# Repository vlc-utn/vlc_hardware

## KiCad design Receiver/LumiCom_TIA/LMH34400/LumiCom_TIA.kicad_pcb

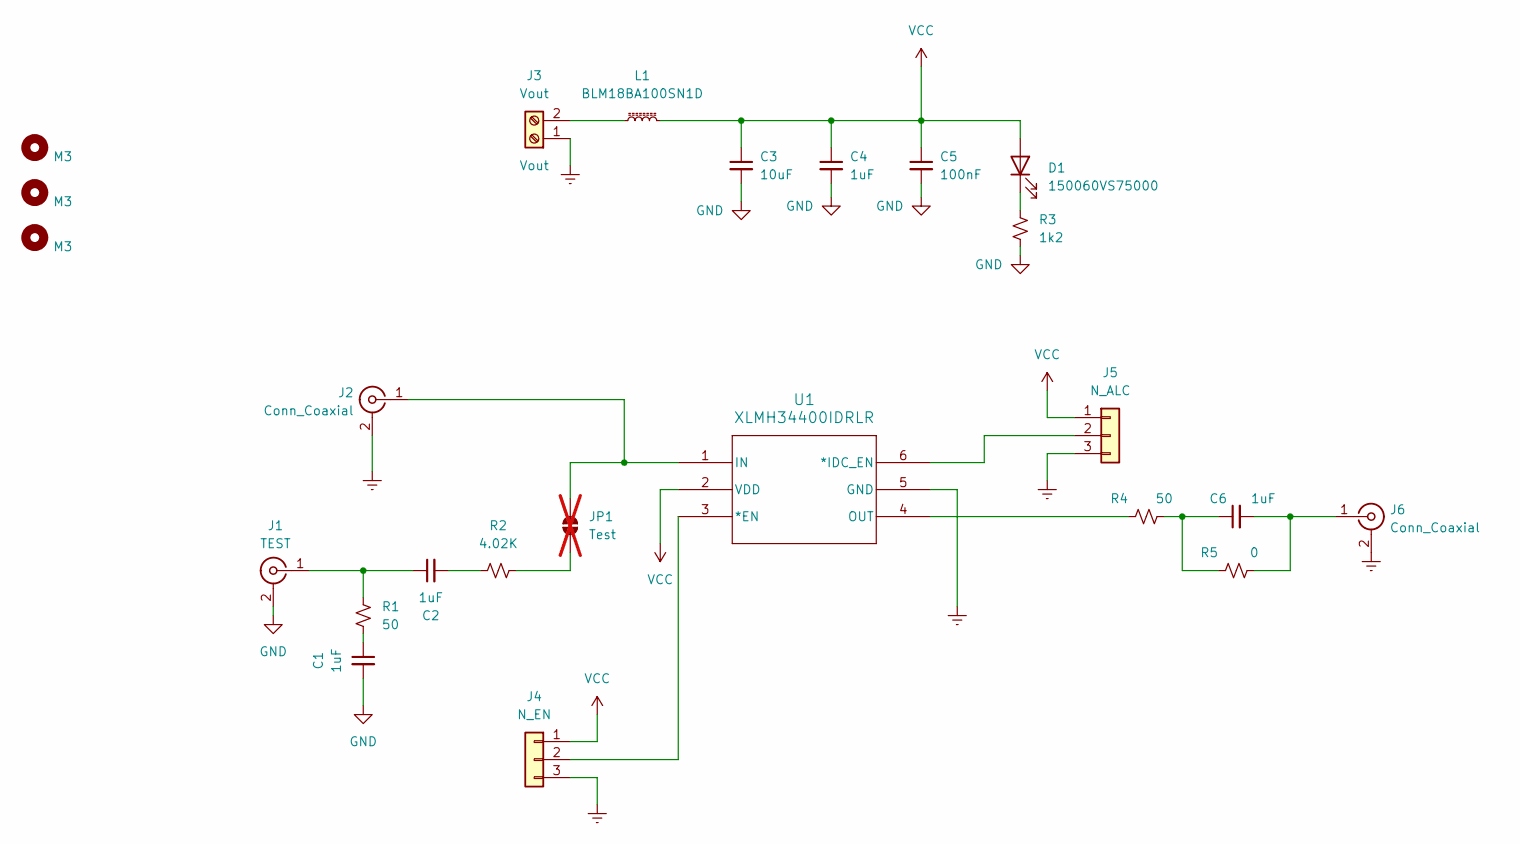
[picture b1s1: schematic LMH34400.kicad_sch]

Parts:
C1, C2, C4, C6: 1uF; C_0603_1608Metric_Pad1.08x0.95mm_HandSolder
C3: 10uF; C_0603_1608Metric_Pad1.08x0.95mm_HandSolder
C5: 100nF; C_0603_1608Metric_Pad1.08x0.95mm_HandSolder
D1: 150060VS75000; LEDC1608X80N
H1, H2, H3: M3; MountingHole_3.2mm_M3_DIN965
J1: TEST; SMA_Samtec_SMA-J-P-X-ST-EM1_EdgeMount
J2, J6: Conn_Coaxial; SMA_Samtec_SMA-J-P-X-ST-EM1_EdgeMount
J3: Vout; TerminalBlock_Phoenix_MKDS-1,5-2_1x02_P5.00mm_Horizontal
J4: N_EN; PinHeader_1x03_P2.54mm_Vertical
J5: N_ALC; PinHeader_1x03_P2.54mm_Vertical
JP1: Test; R_0603_1608Metric_Pad0.98x0.95mm_HandSolder; not fitted
L1: BLM18BA100SN1D; L_0603_1608Metric_Pad1.05x0.95mm_HandSolder
R1, R4: 50; R_0603_1608Metric_Pad0.98x0.95mm_HandSolder
R2: 4.02K; R_0603_1608Metric_Pad0.98x0.95mm_HandSolder
R3: 1k2; R_0603_1608Metric_Pad0.98x0.95mm_HandSolder
R5: 0; R_0603_1608Metric_Pad0.98x0.95mm_HandSolder
U1: XLMH34400IDRLR; SOT5X3-6_DRL_TEX

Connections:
GND: C1.2, C3.2, C4.2, C5.2, J1.2 (Ext), J2.2 (Ext), J3.1, J4.3, J5.3, J6.2 (Ext), R3.2, U1.5 (GND)
unnamed: C1.1, R1.2
unnamed: C2.2, R2.1
unnamed: C6.1, R4.2, R5.1
unnamed: D1.1 (K), R3.1
unnamed: C2.1, J1.1 (In), R1.1
unnamed: J2.1 (In), JP1.2 (B), U1.1 (IN)
unnamed: J3.2, L1.1
unnamed: J4.2, U1.3 (*EN)
unnamed: J5.2, U1.6 (*IDC_EN)
unnamed: C6.2, J6.1 (In), R5.2
unnamed: JP1.1 (A), R2.2
unnamed: R4.1, U1.4 (OUT)
VCC: C3.1, C4.1, C5.1, D1.2 (A), J4.1, J5.1, L1.2, U1.2 (VDD)

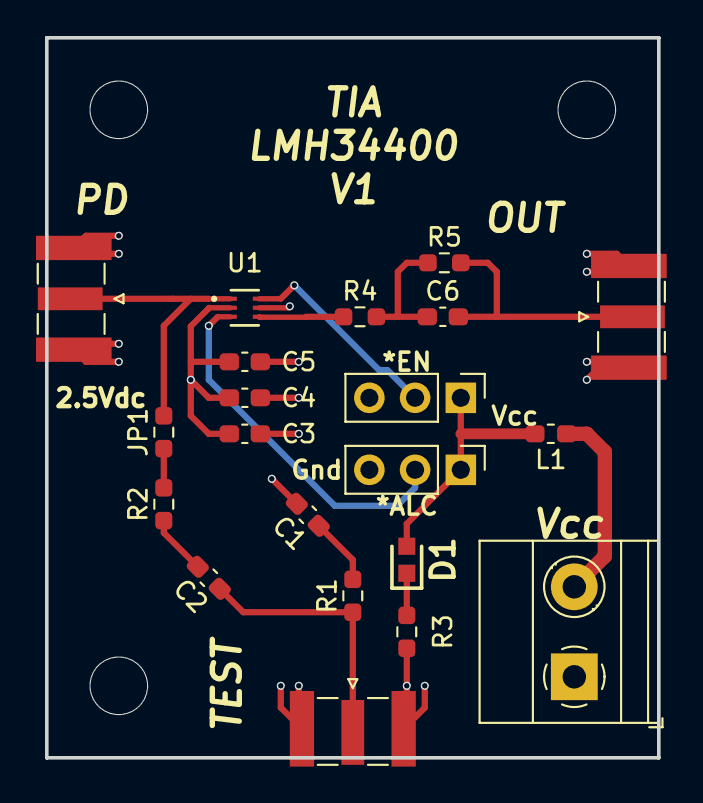
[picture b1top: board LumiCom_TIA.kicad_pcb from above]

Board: 4 copper layers, 34.0 x 40.0 mm, 24 parts (0 on the bottom side), 14 nets.

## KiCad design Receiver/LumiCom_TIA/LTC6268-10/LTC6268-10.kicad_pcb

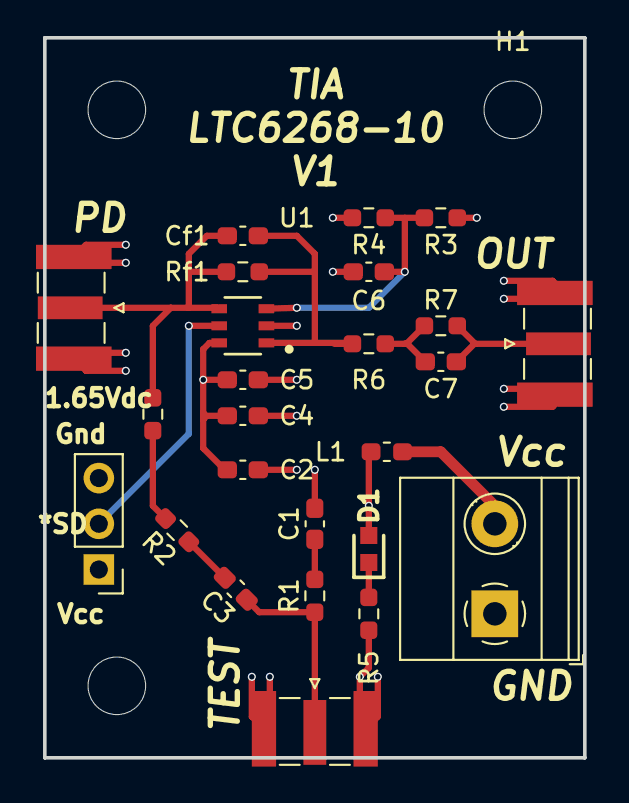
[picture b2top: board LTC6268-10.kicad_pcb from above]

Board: 4 copper layers, 30.0 x 40.0 mm, 28 parts (0 on the bottom side), 14 nets.

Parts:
C1, C3, C4, C7: 1uF; C_0603_1608Metric_Pad1.08x0.95mm_HandSolder
C2, C6: 10uF; C_0603_1608Metric_Pad1.08x0.95mm_HandSolder
C5: 100nF; C_0603_1608Metric_Pad1.08x0.95mm_HandSolder
Cf1: 10uF; C_0603_1608Metric_Pad1.08x0.95mm_HandSolder
D1: 150060VS75000; LEDC1608X80N
H1, H2, H3: M3; MountingHole_3.2mm_M3_DIN965
J1: IN; SMA_Samtec_SMA-J-P-X-ST-EM1_EdgeMount
J2: Vout; TerminalBlock_Phoenix_MKDS-1,5-2_1x02_P5.00mm_Horizontal
J3: TEST; SMA_Samtec_SMA-J-P-X-ST-EM1_EdgeMount
J4: OUT; SMA_Samtec_SMA-J-P-X-ST-EM1_EdgeMount
JP1: Test; R_0603_1608Metric_Pad0.98x0.95mm_HandSolder
L1: BLM18BA100SN1D; L_0603_1608Metric_Pad1.05x0.95mm_HandSolder
R1, R6: 50; R_0603_1608Metric_Pad0.98x0.95mm_HandSolder
R2: 4.02K; R_0603_1608Metric_Pad0.98x0.95mm_HandSolder
R3, R4: 20k; R_0603_1608Metric_Pad0.98x0.95mm_HandSolder
R5: 1k2; R_0603_1608Metric_Pad0.98x0.95mm_HandSolder
R7: 0; R_0603_1608Metric_Pad0.98x0.95mm_HandSolder
Rf1: 10K; R_0603_1608Metric_Pad0.98x0.95mm_HandSolder
SD_L1: SD_L; PinHeader_1x03_P2.54mm_Vertical
U1: LTC6268-10-SOT23; TSOT-23_S6_LIT

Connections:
/Shutdown_L: SD_L1.2 (C), U1.5 (*SHDN)
GND: C1.2, C2.2, C4.2, C5.2, C6.2, J1.2 (Ext), J2.1, J3.2 (Ext), J4.2 (Ext), R4.2, R5.2, SD_L1.3 (B), U1.2 (V-)
unnamed: C1.1, R1.2
unnamed: C3.2, R2.1
unnamed: C7.1, R6.2, R7.1
unnamed: D1.1 (K), R5.1
unnamed: Cf1.1, J1.1 (In), JP1.2 (B), Rf1.1, U1.4 (-IN)
unnamed: J2.2, L1.1
unnamed: C3.1, J3.1 (In), R1.1
unnamed: C7.2, J4.1 (In), R7.2
unnamed: JP1.1 (A), R2.2
unnamed: C6.1, R3.2, R4.1, U1.3 (+IN)
unnamed: Cf1.2, R6.1, Rf1.2, U1.1 (OUT)
VCC: C2.1, C4.1, C5.1, D1.2 (A), L1.2, R3.1, SD_L1.1 (A), U1.6 (V+)

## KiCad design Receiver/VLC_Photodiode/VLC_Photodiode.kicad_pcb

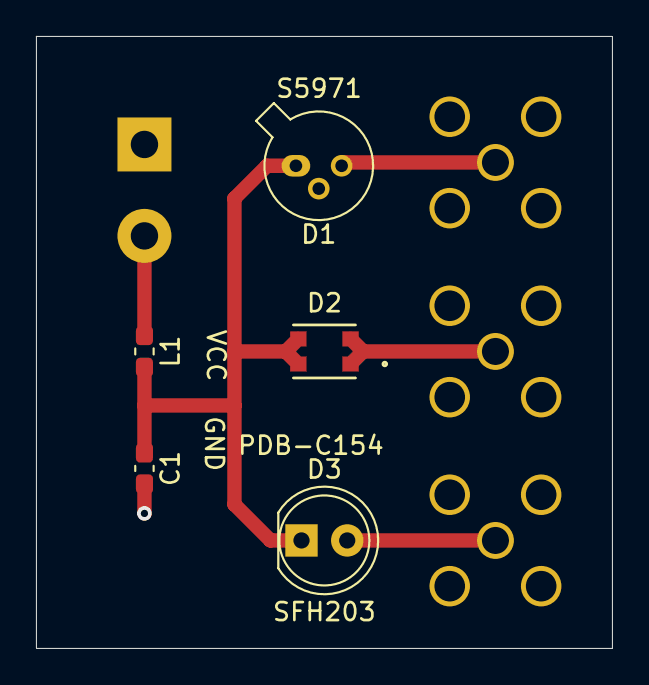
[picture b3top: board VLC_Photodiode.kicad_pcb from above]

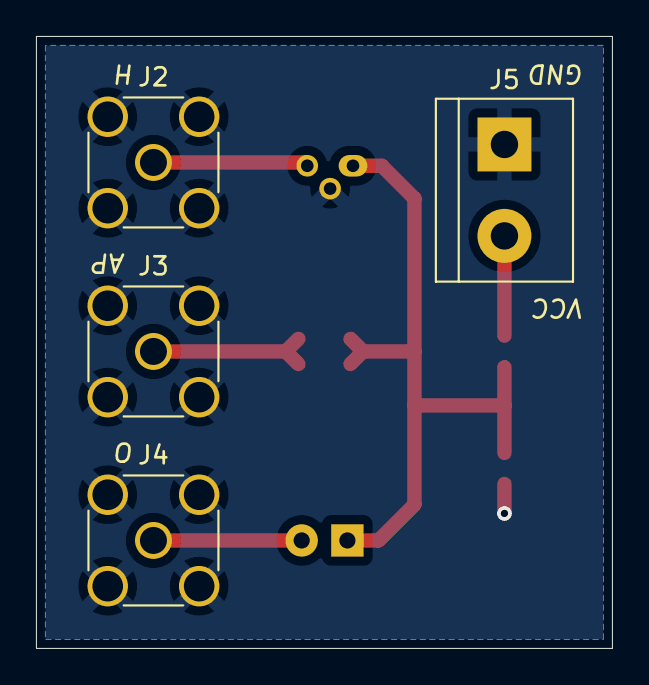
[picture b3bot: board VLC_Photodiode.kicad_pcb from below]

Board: 2 copper layers, 32.0 x 34.0 mm, 9 parts (4 on the bottom side), 6 nets.

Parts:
C1: 10uF; C_0603_1608Metric_Pad1.08x0.95mm_HandSolder
D1: S5971; TO-18-3
D2: PDB-C154SM; PDB-C154SM_ADP
D3: SFH203; LED_D5.0mm_IRGrey
J2, J3, J4: RFPC-SMA28-F
J5: Screw_Terminal_01x02; TerminalBlock_bornier-2_P5.08mm
L1: BLM18BA100SN1D; L_0603_1608Metric_Pad1.05x0.95mm_HandSolder

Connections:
GND: C1.2, D1.2 (C), J2.2 (Ext), J3.2 (Ext), J4.2 (Ext), J5.1
unnamed: D1.3 (A), J2.1 (In)
unnamed: C1.1, D1.1 (K), D2.3 (CATHODE), D2.4 (CATHODE), D3.1 (K), L1.2
unnamed: D3.2 (A), J4.1 (In)
unnamed: D2.1 (ANODE), D2.2 (ANODE), J3.1 (In)
unnamed: J5.2, L1.1

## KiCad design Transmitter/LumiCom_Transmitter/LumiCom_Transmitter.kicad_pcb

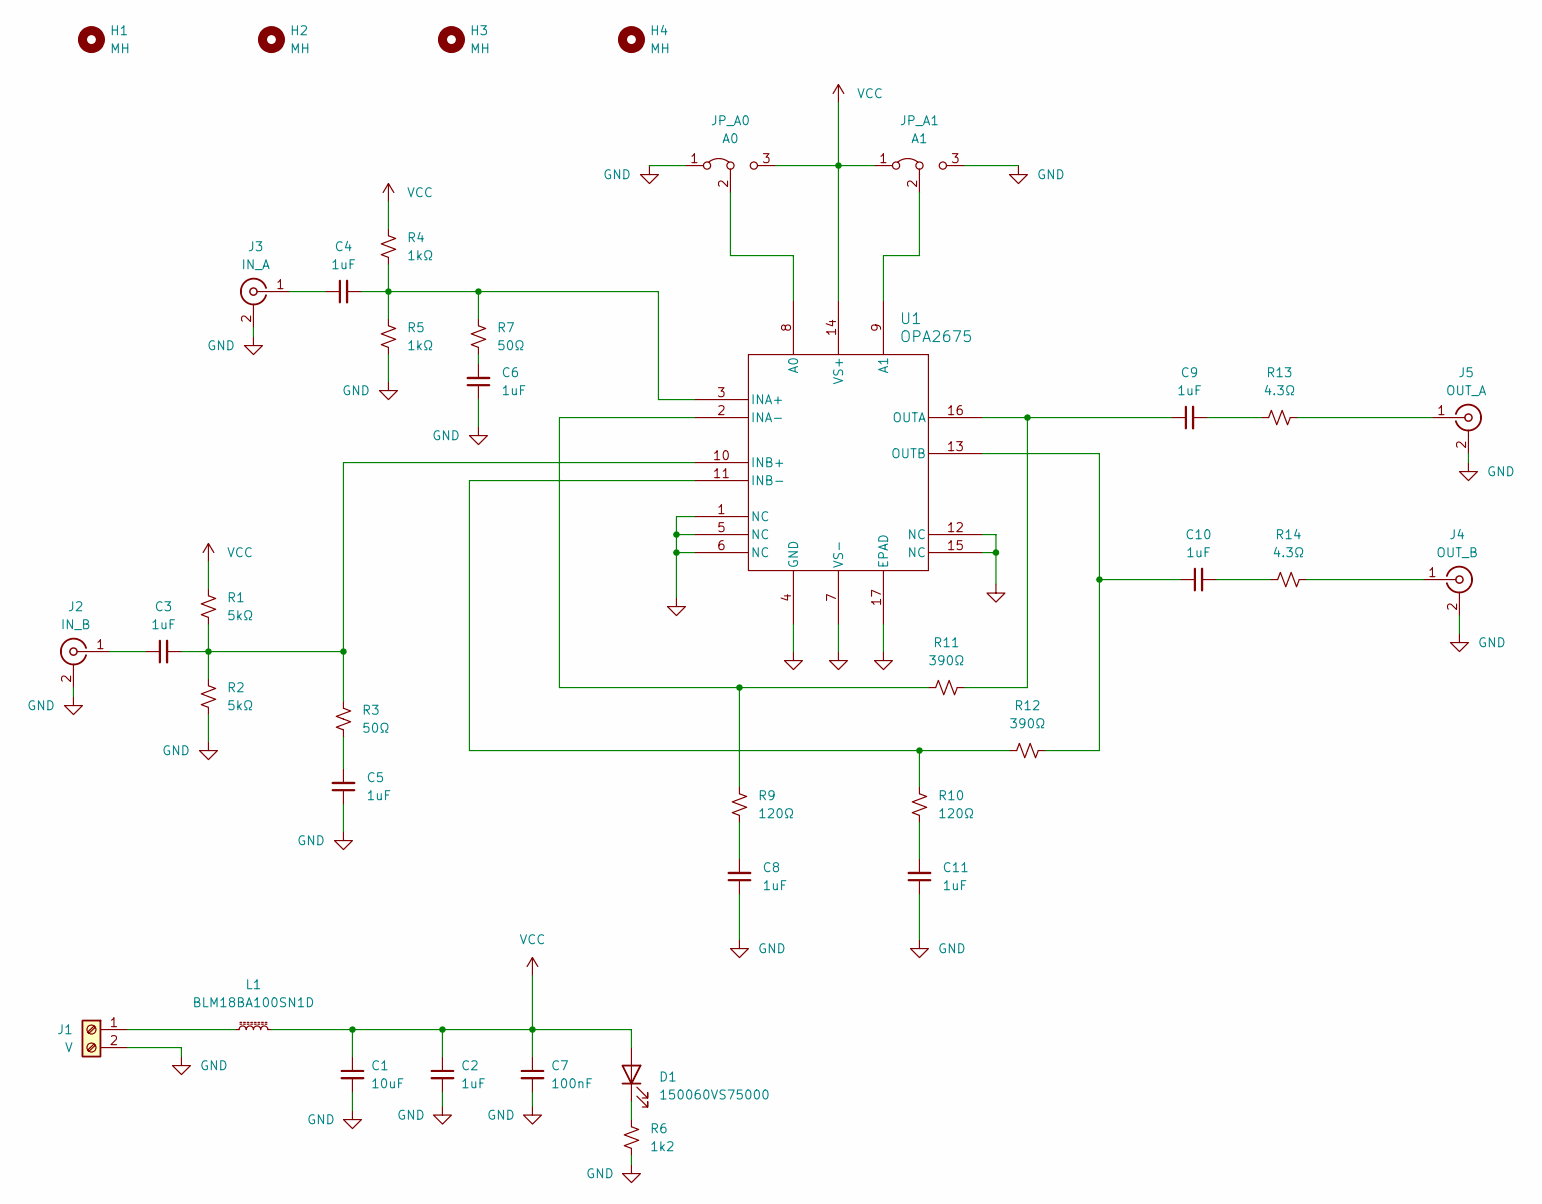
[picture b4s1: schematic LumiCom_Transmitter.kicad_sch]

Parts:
C1: 10uF; C_0603_1608Metric_Pad1.08x0.95mm_HandSolder
C2: 1uF; C_0603_1608Metric_Pad1.08x0.95mm_HandSolder
C3, C4, C5, C6, C8, C11: 1uF; C_0603_1608Metric; LCSC C19702
C7: 100nF; C_0603_1608Metric_Pad1.08x0.95mm_HandSolder
C9, C10: 1uF; C_0603_1608Metric; LCSC C14663
D1: 150060VS75000; LEDC1608X80N
H1, H2, H3, H4: MH; MountingHole_3.2mm_M3_ISO7380
J1: V; TerminalBlock_Phoenix_MKDS-1,5-2_1x02_P5.00mm_Horizontal
J2: IN_B; SMA_Samtec_SMA-J-P-X-ST-EM1_EdgeMount
J3: IN_A; SMA_Samtec_SMA-J-P-X-ST-EM1_EdgeMount
J4: OUT_B; SMA_Samtec_SMA-J-P-X-ST-EM1_EdgeMount
J5: OUT_A; SMA_Samtec_SMA-J-P-X-ST-EM1_EdgeMount
JP_A0: A0; PinHeader_1x03_P2.54mm_Vertical
JP_A1: A1; PinHeader_1x03_P2.54mm_Vertical
L1: BLM18BA100SN1D; L_0603_1608Metric_Pad1.05x0.95mm_HandSolder
R1, R2: 5kΩ; R_0603_1608Metric; LCSC C21190
R3, R7: 50Ω; R_0603_1608Metric; LCSC C23185
R4, R5: 1kΩ; R_0603_1608Metric; LCSC C21190
R6: 1k2; R_0603_1608Metric_Pad0.98x0.95mm_HandSolder
R9, R10: 120Ω; R_0603_1608Metric; LCSC C22787
R11, R12: 390Ω; R_0603_1608Metric; LCSC C23151
R13, R14: 4.3Ω; R_1210_3225Metric_Pad1.30x2.65mm_HandSolder; LCSC C102477
U1: OPA2675; Texas_RGV0016A_VQFN-16-1EP_4x4mm_P0.65mm_EP2.1x2.1mm_Therma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; LCSC C19711669

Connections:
GND: C1.2, C2.2, C5.1, C6.1, C7.2, C8.1, C11.1, J1.2, J2.2 (Ext), J3.2 (Ext), J4.2 (Ext), J5.2 (Ext), JP_A0.1 (A), JP_A1.3 (B), R2.2, R5.2, R6.2, U1.1 (NC), U1.4 (GND), U1.5 (NC), U1.6 (NC), U1.7 (VS-), U1.12 (NC), U1.15 (NC), U1.17 (EPAD)
unnamed: C5.2, R3.2
unnamed: C6.2, R7.2
unnamed: C8.2, R9.1
unnamed: C9.2, R13.1
unnamed: C10.2, R14.1
unnamed: C11.2, R10.1
unnamed: D1.1 (K), R6.1
unnamed: J1.1, L1.1
unnamed: C3.1, J2.1 (In)
unnamed: C4.1, J3.1 (In)
unnamed: J4.1 (In), R14.2
unnamed: J5.1 (In), R13.2
unnamed: JP_A0.2 (C), U1.8 (A0)
unnamed: JP_A1.2 (C), U1.9 (A1)
unnamed: C4.2, R4.2, R5.1, R7.1, U1.3 (INA+)
unnamed: R9.2, R11.1, U1.2 (INA-)
unnamed: C3.2, R1.2, R2.1, R3.1, U1.10 (INB+)
unnamed: R10.2, R12.1, U1.11 (INB-)
unnamed: C9.1, R11.2, U1.16 (OUTA)
unnamed: C10.1, R12.2, U1.13 (OUTB)
VCC: C1.1, C2.1, C7.1, D1.2 (A), JP_A0.3 (B), JP_A1.1 (A), L1.2, R1.1, R4.1, U1.14 (VS+)

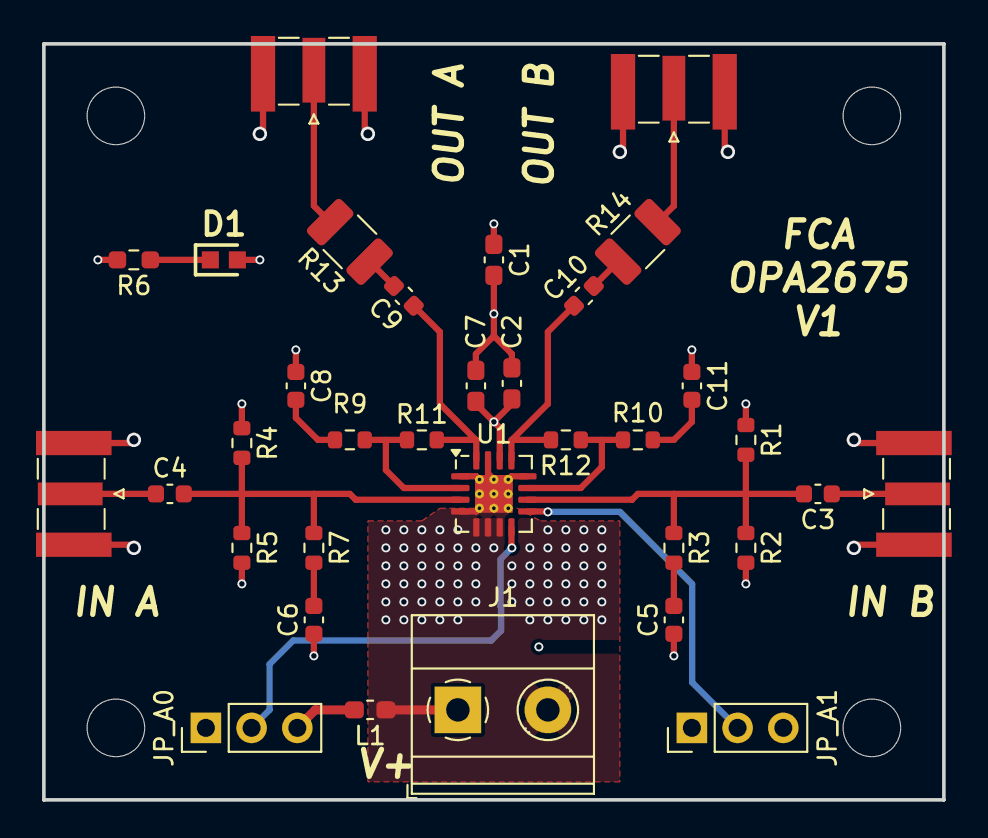
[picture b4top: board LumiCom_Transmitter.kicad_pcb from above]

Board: 4 copper layers, 50.0 x 42.0 mm, 38 parts (0 on the bottom side), 22 nets.

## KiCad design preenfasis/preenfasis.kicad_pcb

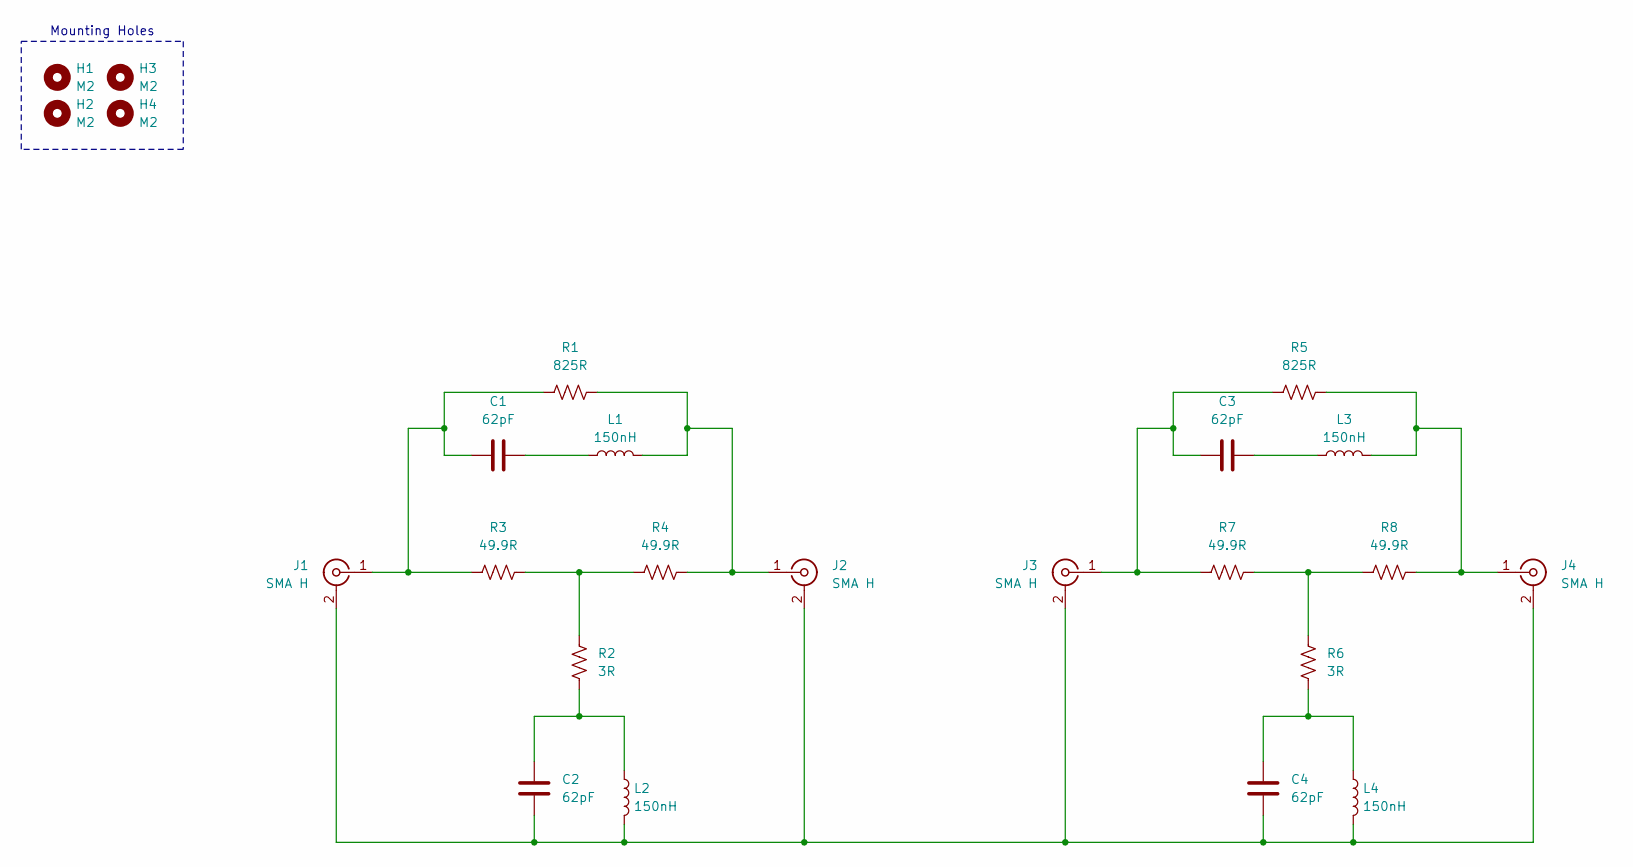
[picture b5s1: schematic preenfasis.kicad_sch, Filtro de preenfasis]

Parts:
C1, C2, C3, C4: 62pF; C_0603_1608Metric_Pad1.08x0.95mm_HandSolder; Manufacturer P/N CC0603JRNPO9BN620; Mouser P/N 603-CC603JRNPO9BN620
H1, H2, H3, H4: M2; MountingHole_2.2mm_M2_ISO7380; Manufacturer P/N N/A; Mouser P/N N/A
J1, J2, J3, J4: SMA H; SMA_Samtec_SMA-J-P-X-ST-EM1_EdgeMount; Manufacturer P/N Electrocomponentes; Mouser P/N N/A
L1, L2, L3, L4: 150nH; L_0603_1608Metric_Pad1.05x0.95mm_HandSolder; Manufacturer P/N MLJ1608WR15JT000; Mouser P/N 810-MLJ1608WR15JT000
R1, R5: 825R; R_0603_1608Metric_Pad0.98x0.95mm_HandSolder; Manufacturer P/N RT0603FRE07825RL; Mouser P/N 603-RT0603FRE07825RL
R2, R6: 3R; R_0603_1608Metric_Pad0.98x0.95mm_HandSolder; Manufacturer P/N RT0603FRE073RL; Mouser P/N 603-RT0603FRE073RL
R3, R4, R7, R8: 49.9R; R_0603_1608Metric_Pad0.98x0.95mm_HandSolder; Manufacturer P/N RT0603FRE0749R9L; Mouser P/N 603-RT0603FRE0749R9L

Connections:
unnamed: C1.2, L1.1
unnamed: C2.2, L2.1, R2.2
unnamed: C3.2, L3.1
unnamed: C4.2, L4.1, R6.2
unnamed: C2.1, C4.1, J1.2 (Ext), J2.2 (Ext), J3.2 (Ext), J4.2 (Ext), L2.2, L4.2
unnamed: C1.1, J1.1 (In), R1.1, R3.1
unnamed: J2.1 (In), L1.2, R1.2, R4.2
unnamed: C3.1, J3.1 (In), R5.1, R7.1
unnamed: J4.1 (In), L3.2, R5.2, R8.2
unnamed: R2.1, R3.2, R4.1
unnamed: R6.1, R7.2, R8.1

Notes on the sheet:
Mounting Holes

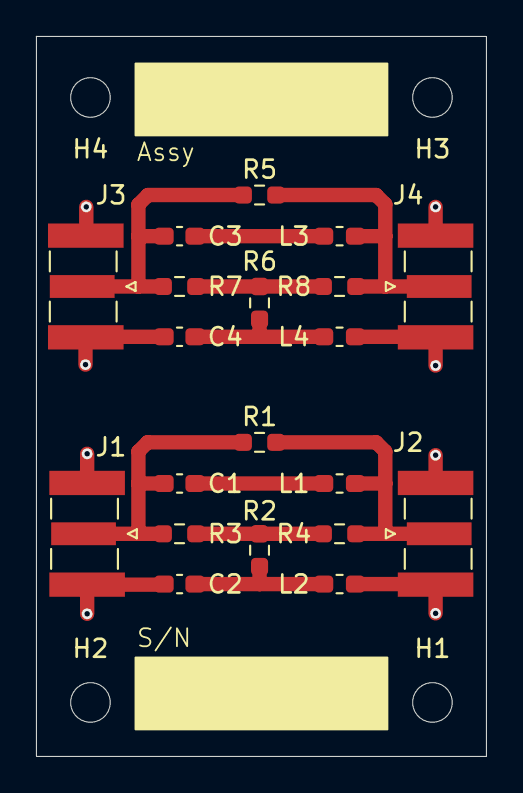
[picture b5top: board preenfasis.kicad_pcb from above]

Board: 2 copper layers, 25.0 x 40.0 mm, 24 parts (0 on the bottom side), 11 nets.

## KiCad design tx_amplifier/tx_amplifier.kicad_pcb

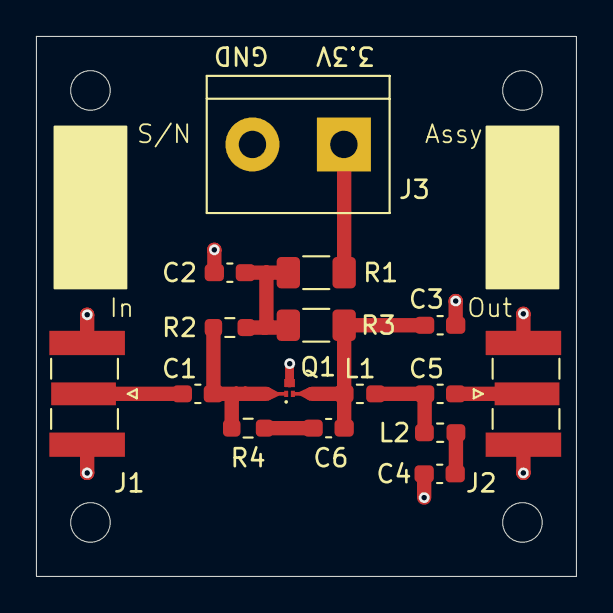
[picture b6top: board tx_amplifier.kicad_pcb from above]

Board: 2 copper layers, 30.0 x 30.0 mm, 20 parts (0 on the bottom side), 10 nets.

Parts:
C1, C5: 1uF; C_0603_1608Metric_Pad1.08x0.95mm_HandSolder
C2, C6: 220nF; C_0603_1608Metric_Pad1.08x0.95mm_HandSolder
C3: 8.2pF; C_0603_1608Metric_Pad1.08x0.95mm_HandSolder
C4: 4.7pF; C_0603_1608Metric_Pad1.08x0.95mm_HandSolder
H1, H2, H3, H4: M2; MountingHole_2.2mm_M2_ISO7380
J1, J2: Conn_Coaxial; SMA_Samtec_SMA-J-P-X-ST-EM1_EdgeMount
J3: Screw_Terminal_01x02; TerminalBlock_bornier-2_P5.08mm
L1: 22nH; L_0603_1608Metric_Pad1.05x0.95mm_HandSolder
L2: 9.1nH; L_0603_1608Metric_Pad1.05x0.95mm_HandSolder
Q1: BFR740L3RH; TSLP-3-9
R1: 47R; R_1206_3216Metric_Pad1.30x1.75mm_HandSolder
R2: 39k; R_0603_1608Metric_Pad0.98x0.95mm_HandSolder
R3: 160R; R_1206_3216Metric_Pad1.30x1.75mm_HandSolder
R4: 910R; R_0603_1608Metric_Pad0.98x0.95mm_HandSolder

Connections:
+3.3V: J3.1, R1.2
GND: C2.2, C3.1, C4.1, J1.2 (Ext), J2.2 (Ext), J3.2, Q1.3 (E)
unnamed: C2.1, R1.1, R2.2, R3.2
unnamed: C4.2, L2.2
unnamed: C5.1, L1.2, L2.1
unnamed: C6.1, R4.1
unnamed: C1.1, J1.1 (In)
unnamed: C5.2, J2.1 (In)
unnamed: C1.2, Q1.1 (B), R2.1, R4.2
unnamed: C3.2, C6.2, L1.1, Q1.2 (C), R3.1
